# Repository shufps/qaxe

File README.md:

# NerdQ Hardware Repository

This repository contains multiple generations of small-scale Bitcoin miner hardware designs.

## NerdQAxe++

Current high-performance design based on 4× BM1370 ASICs.

- ~4.8 TH/s at ~76 W (~15.8 J/TH)
- Previous stable version (that was used for most NQ++): [rev5.1](https://github.com/shufps/qaxe/releases/tag/rev5.1)
- Latest:  [rev5.1.2](https://github.com/shufps/qaxe/releases/tag/rev5.1.2)*

*: contains some [improvements](https://github.com/shufps/qaxe/pull/31) but is untested yet.

## NerdQAxe+

Design based on 4x BM1368 ASICs.

- ~2.5TH/s at ~55 W (~22 J/TH)
- Latest revision 5.0

## Firmware for NQ+ and NQ++

The latest version can be found here:

https://github.com/shufps/ESP-Miner-NerdQAxePlus

## Legacy Designs

The following designs are **end of life** and no longer supported:

- QAxe+
- QAxe

They are provided for reference, documentation, and historical reasons only.

**No support, fixes, or updates will be provided for legacy designs.**

See `legacy/README.md` for full documentation of deprecated hardware.

---

## Compatible Replacement Parts

### For NerdQAxe++
- 25 MHz Oscillator
  Original: IQD LFSPXO076024
  Replacement: Taitien OXLTDLJANF-25.000000

### For NerdQAxe++ and NerdQAxe+
- 0.8 V LDO
  Original: Microchip MCP1824T-0802E-OT
  Replacement: TI TPS78408QDBVRQ1

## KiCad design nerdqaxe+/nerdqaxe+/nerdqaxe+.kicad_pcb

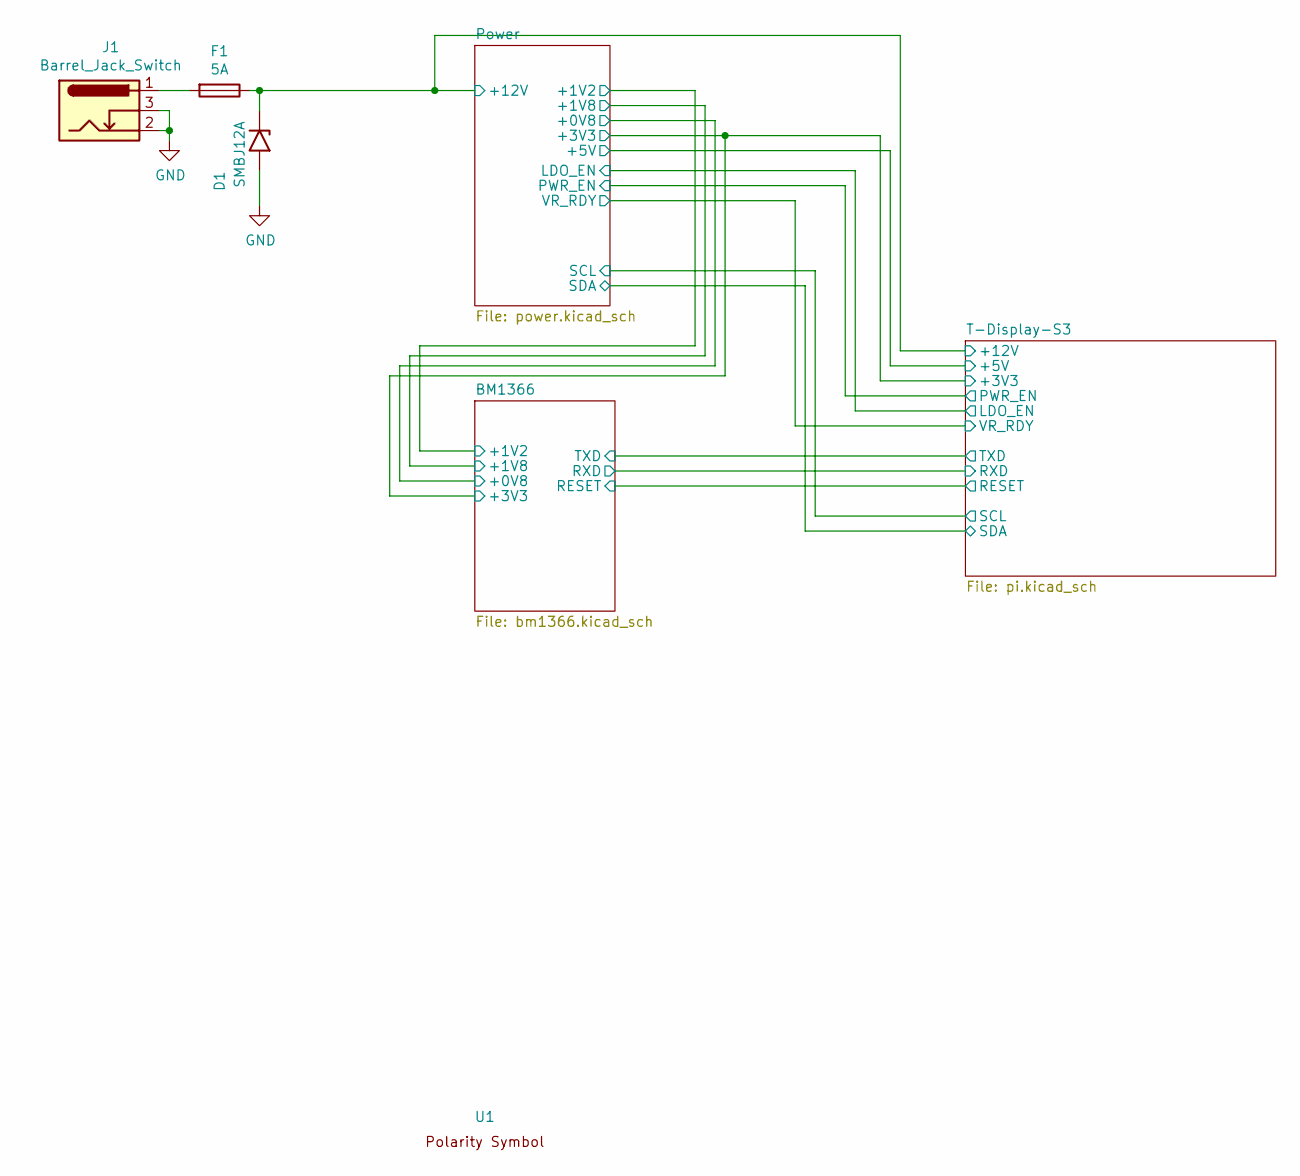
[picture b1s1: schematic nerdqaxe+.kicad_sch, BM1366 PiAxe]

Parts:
D1: SMBJ12A; D_SMB
F1: 5A; fuseholder_littlefuse_blok
J1: Barrel_Jack_Switch; BarrelJack_CUI_PJ-102AH_Horizontal
U1: polarity

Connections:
+12V: D1.1 (A1), F1.1; also elsewhere on the board
GND: D1.2 (A2), J1.2, J1.3; also elsewhere on the board
unnamed: F1.2, J1.1

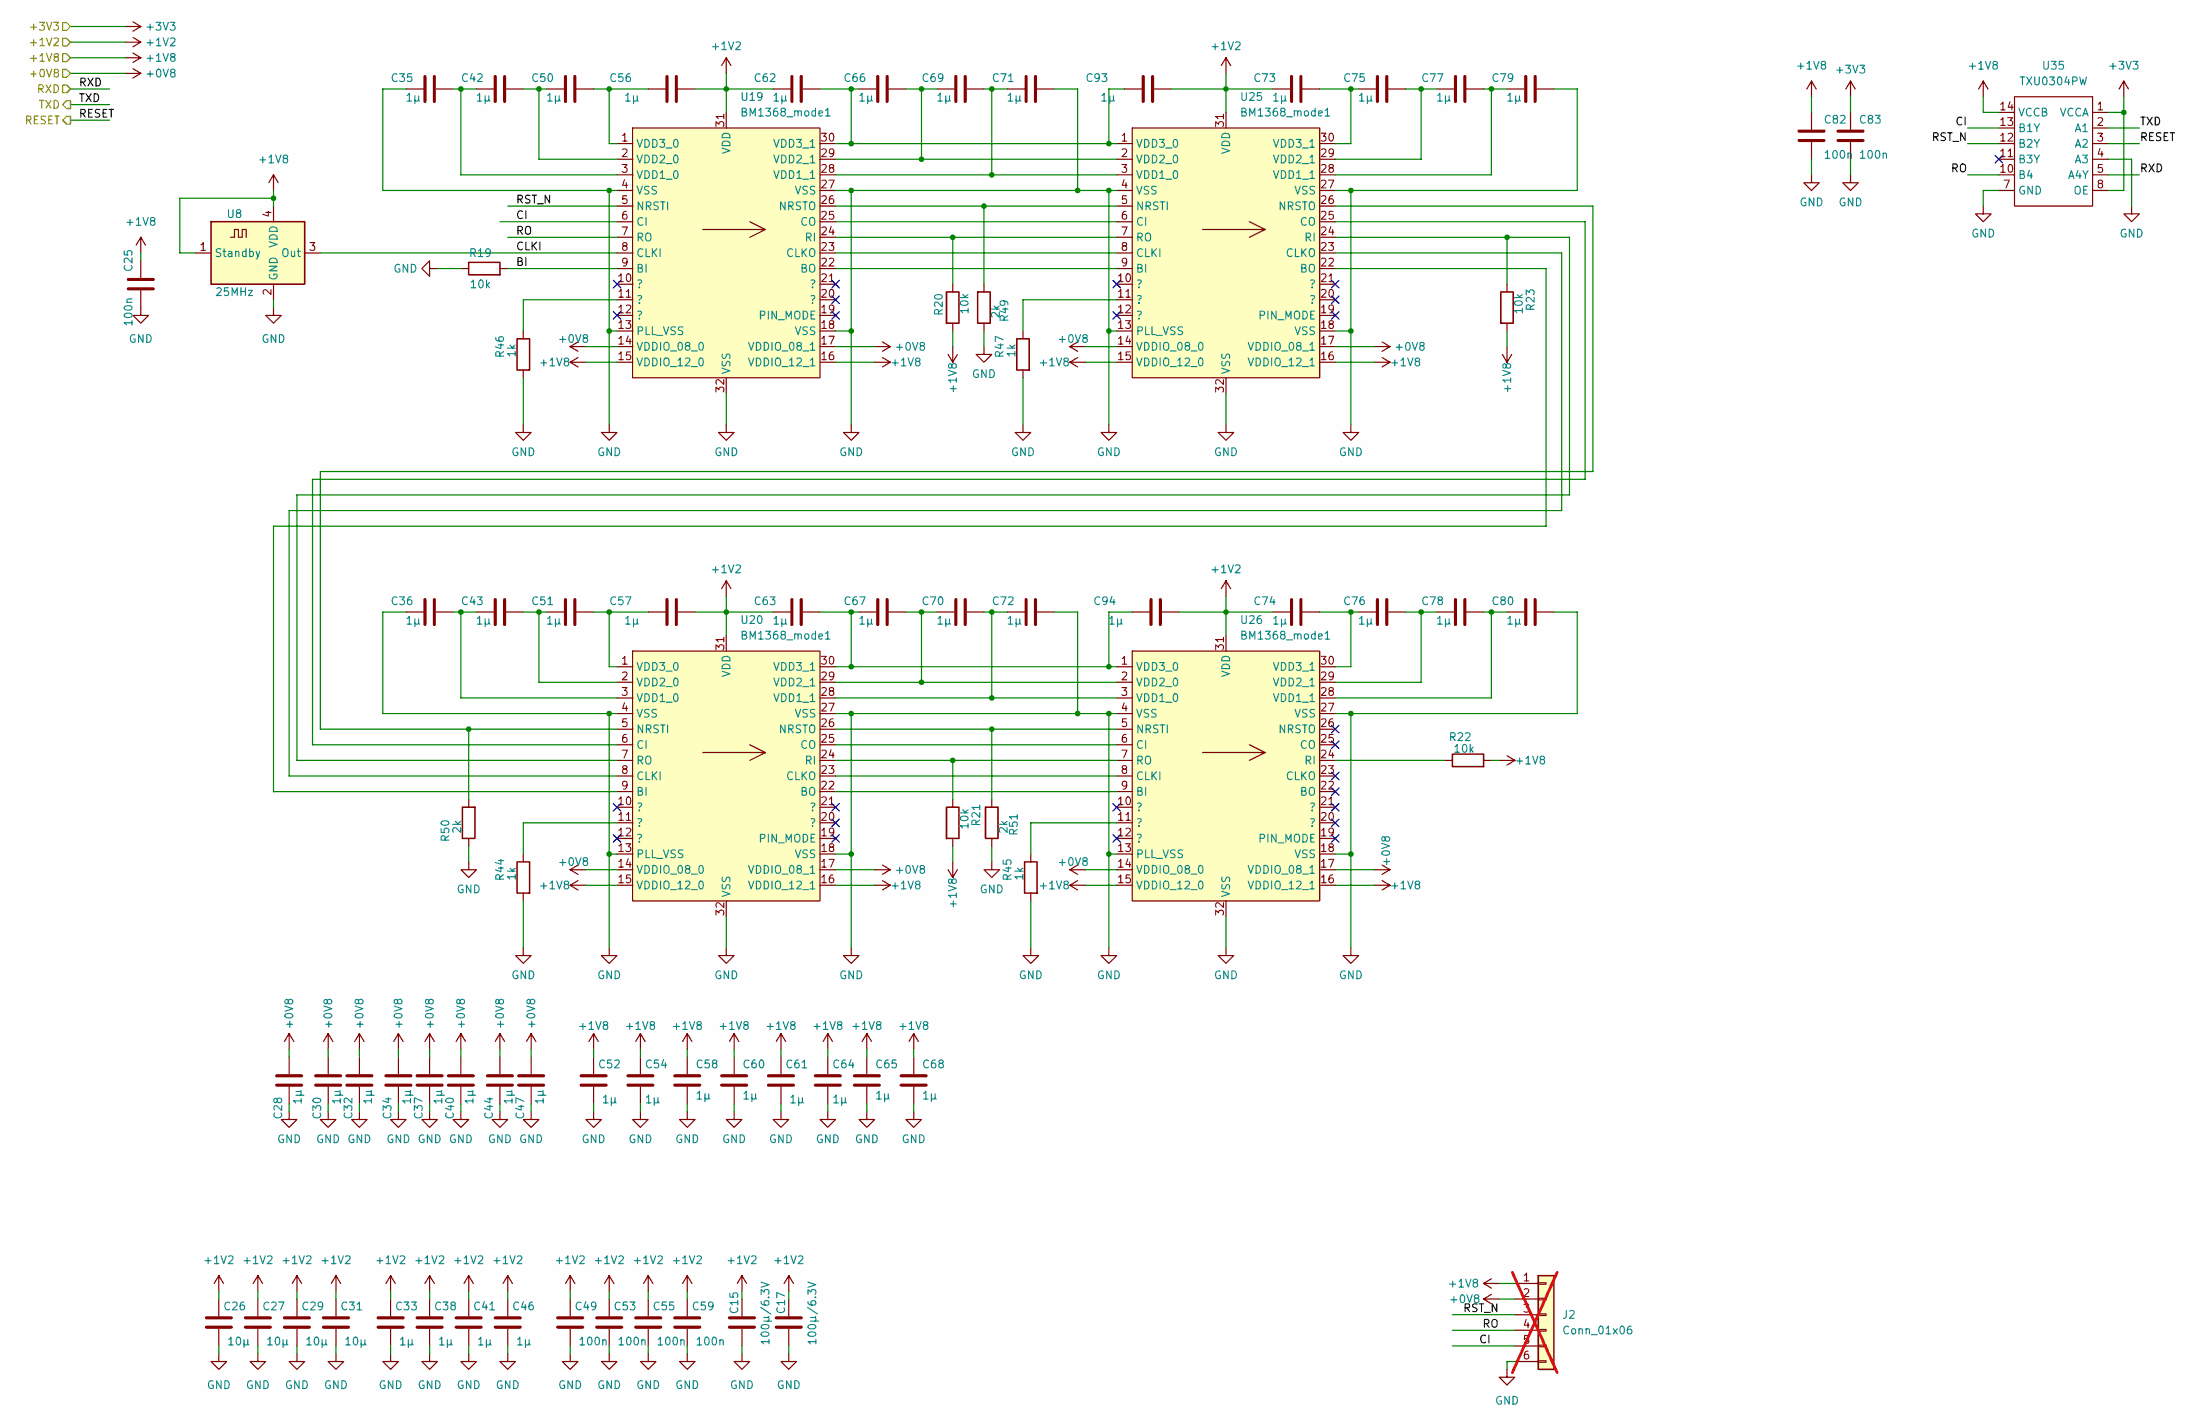
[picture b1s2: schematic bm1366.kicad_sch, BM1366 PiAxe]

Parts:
C15, C17: 100µ/6.3V; C_1210_3225Metric
C25, C49, C53, C55, C59, C82, C83: 100n; C_0805_2012Metric
C26, C27, C29, C31: 10µ; C_0805_2012Metric
C28, C30, C32, C33, C34, C35, C36, C37, C38, C40, C41, C42, C43, C44, C46, C47, C50, C51, C52, C54, C56, C57, C58, C60, C61, C62, C63, C64, C65, C66, C67, C68, C69, C70, C71, C72, C73, C74, C75, C76, C77, C78, C79, C80, C93, C94: 1µ; C_0805_2012Metric
J2: Conn_01x06; PinHeader_1x06_P1.27mm_Vertical; not fitted
R19, R20, R21, R22, R23: 10k; R_0805_2012Metric
R44, R45, R46, R47: 1k; R_0805_2012Metric
R49, R50, R51: 2k; R_0805_2012Metric
U8: 25MHz; Oscillator_SMD_EuroQuartz_XO32-4Pin_3.2x2.5mm
U19, U20, U25, U26: BM1368_mode1; bm1368-package-modified
U35: TXU0304PW; TSSOP-14_4.4x5mm_P0.65mm

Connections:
+0V8: C28.2, C30.2, C32.2, C34.2, C37.2, C40.2, C44.2, C47.2, J2.2, U19.14 (VDDIO_08_0), U19.17 (VDDIO_08_1), U20.14 (VDDIO_08_0), U20.17 (VDDIO_08_1), U25.14 (VDDIO_08_0), U25.17 (VDDIO_08_1), U26.14 (VDDIO_08_0), U26.17 (VDDIO_08_1); also elsewhere on the board
+1V2: C15.1, C17.1, C26.1, C27.1, C29.1, C31.1, C33.1, C38.1, C41.1, C46.1, C49.1, C53.1, C55.1, C56.2, C57.2, C59.1, C62.1, C63.1, C73.1, C74.1, C93.2, C94.2, U19.31 (VDD), U20.31 (VDD), U25.31 (VDD), U26.31 (VDD); also elsewhere on the board
+1V8: C25.1, C52.1, C54.1, C58.1, C60.1, C61.1, C64.1, C65.1, C68.1, C82.1, J2.1, R20.2, R21.2, R22.2, R23.2, U8.1 (Standby), U8.4 (VDD), U19.15 (VDDIO_12_0), U19.16 (VDDIO_12_1), U20.15 (VDDIO_12_0), U20.16 (VDDIO_12_1), U25.15 (VDDIO_12_0), U25.16 (VDDIO_12_1), U26.15 (VDDIO_12_0), U26.16 (VDDIO_12_1), U35.14 (VCCB); also elsewhere on the board
+3V3: C83.1, U35.1 (VCCA), U35.8 (OE); also elsewhere on the board
/BM1366/BI: R19.2, U19.9 (BI)
/BM1366/CI: J2.5, U19.6 (CI), U35.13 (B1Y)
/BM1366/CLKI: U8.3 (Out), U19.8 (CLKI)
/BM1366/RESET: U35.3 (A2); also elsewhere on the board
/BM1366/RO: J2.4, U19.7 (RO), U35.10 (B4)
/BM1366/RST_N: J2.3, U19.5 (NRSTI), U35.12 (B2Y)
/BM1366/RXD: U35.5 (A4Y); also elsewhere on the board
/BM1366/TXD: U35.2 (A1); also elsewhere on the board
GND: C15.2, C17.2, C25.2, C26.2, C27.2, C28.1, C29.2, C30.1, C31.2, C32.1, C33.2, C34.1, C35.1, C36.1, C37.1, C38.2, C40.1, C41.2, C44.1, C46.2, C47.1, C49.2, C52.2, C53.2, C54.2, C55.2, C58.2, C59.2, C60.2, C61.2, C64.2, C65.2, C68.2, C71.2, C72.2, C79.2, C80.2, C82.2, C83.2, J2.6, R19.1, R44.2, R45.2, R46.2, R47.2, R49.1, R50.1, R51.1, U8.2 (GND), U19.4 (VSS), U19.13 (PLL_VSS), U19.18 (VSS), U19.27 (VSS), U19.32 (VSS), U20.4 (VSS), U20.13 (PLL_VSS), U20.18 (VSS), U20.27 (VSS), U20.32 (VSS), U25.4 (VSS), U25.13 (PLL_VSS), U25.18 (VSS), U25.27 (VSS), U25.32 (VSS), U26.4 (VSS), U26.13 (PLL_VSS), U26.18 (VSS), U26.27 (VSS), U26.32 (VSS), U35.4 (A3), U35.7 (GND); also elsewhere on the board
unnamed: R44.1, U20.11 (?)
unnamed: R45.1, U26.11 (?)
unnamed: R46.1, U19.11 (?)
unnamed: R47.1, U25.11 (?)
unnamed: U19.22 (BO), U25.9 (BI)
unnamed: U19.23 (CLKO), U25.8 (CLKI)
unnamed: U19.25 (CO), U25.6 (CI)
unnamed: R49.2, U19.26 (NRSTO), U25.5 (NRSTI)
unnamed: R20.1, U19.24 (RI), U25.7 (RO)
unnamed: C35.2, C42.1, U19.3 (VDD1_0)
unnamed: C69.2, C71.1, U19.28 (VDD1_1), U25.3 (VDD1_0)
unnamed: C42.2, C50.1, U19.2 (VDD2_0)
unnamed: C66.2, C69.1, U19.29 (VDD2_1), U25.2 (VDD2_0)
unnamed: C50.2, C56.1, U19.1 (VDD3_0)
unnamed: C62.2, C66.1, C93.1, U19.30 (VDD3_1), U25.1 (VDD3_0)
unnamed: U20.9 (BI), U25.22 (BO)
unnamed: U20.22 (BO), U26.9 (BI)
unnamed: U20.6 (CI), U25.25 (CO)
unnamed: U20.8 (CLKI), U25.23 (CLKO)
unnamed: U20.23 (CLKO), U26.8 (CLKI)
unnamed: U20.25 (CO), U26.6 (CI)
unnamed: R50.2, U20.5 (NRSTI), U25.26 (NRSTO)
unnamed: R51.2, U20.26 (NRSTO), U26.5 (NRSTI)
unnamed: R21.1, U20.24 (RI), U26.7 (RO)
unnamed: R23.1, U20.7 (RO), U25.24 (RI)
unnamed: C36.2, C43.1, U20.3 (VDD1_0)
unnamed: C70.2, C72.1, U20.28 (VDD1_1), U26.3 (VDD1_0)
unnamed: C43.2, C51.1, U20.2 (VDD2_0)
unnamed: C67.2, C70.1, U20.29 (VDD2_1), U26.2 (VDD2_0)
unnamed: C51.2, C57.1, U20.1 (VDD3_0)
unnamed: C63.2, C67.1, C94.1, U20.30 (VDD3_1), U26.1 (VDD3_0)
unnamed: C77.2, C79.1, U25.28 (VDD1_1)
unnamed: C75.2, C77.1, U25.29 (VDD2_1)
unnamed: C73.2, C75.1, U25.30 (VDD3_1)
unnamed: R22.1, U26.24 (RI)
unnamed: C78.2, C80.1, U26.28 (VDD1_1)
unnamed: C76.2, C78.1, U26.29 (VDD2_1)
unnamed: C74.2, C76.1, U26.30 (VDD3_1)

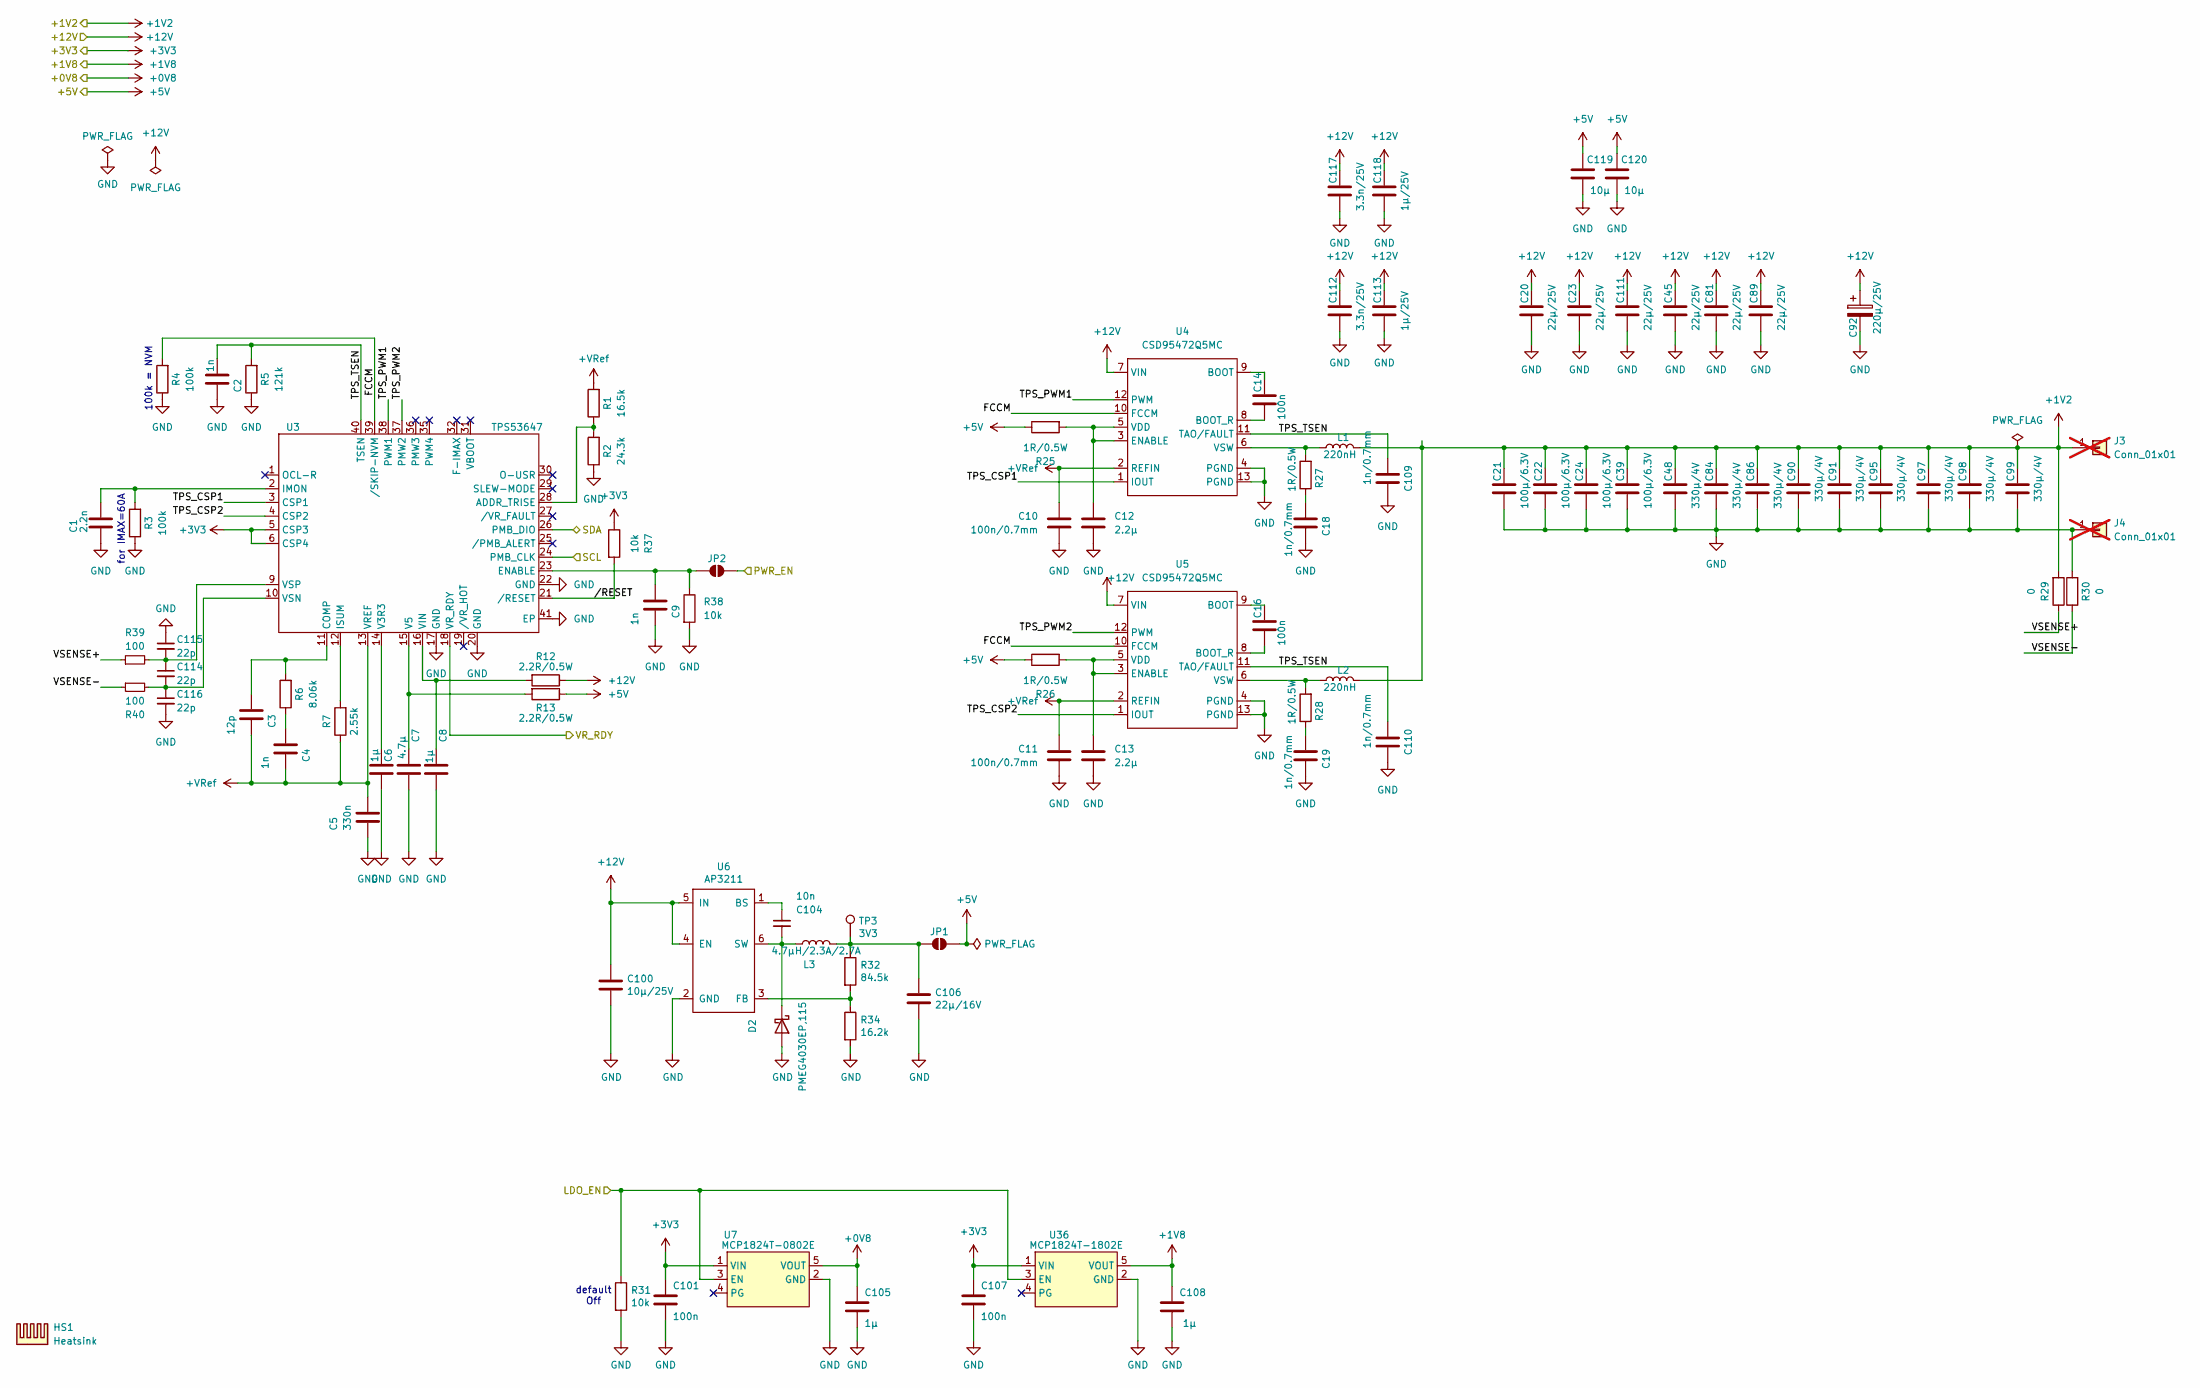
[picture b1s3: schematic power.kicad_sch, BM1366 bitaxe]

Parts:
C1: 2.2n; C_0805_2012Metric
C2, C4, C9: 1n; C_0805_2012Metric
C3: 12p; C_0603_1608Metric
C5: 330n; C_0805_2012Metric
C6, C8, C105, C108: 1µ; C_0805_2012Metric
C7: 4.7µ; C_0805_2012Metric
C10, C11: 100n/0.7mm; C_0805_2012Metric
C12, C13: 2.2µ; C_0805_2012Metric
C14, C16, C101, C107: 100n; C_0805_2012Metric
C18, C19, C109, C110: 1n/0.7mm; C_0805_2012Metric
C20, C23, C45, C81, C89, C111: 22µ/25V; C_1210_3225Metric
C21, C22, C24, C39: 100µ/6.3V; C_1210_3225Metric
C48, C84, C86, C90, C91, C95, C97, C98, C99: 330µ/4V; C_1210_3225Metric
C92: 220µ/25V; CP_Elec_8x10
C100: 10µ/25V; C_0805_2012Metric
C104: 10n; C_0805_2012Metric
C106: 22µ/16V; C_1206_3216Metric
C112, C117: 3.3n/25V; C_0805_2012Metric
C113, C118: 1µ/25V; C_0805_2012Metric
C114, C115, C116: 22p; C_0603_1608Metric
C119, C120: 10µ; C_0805_2012Metric
D2: PMEG4030EP,115; D_SOD-128
HS1: Heatsink
J3, J4: Conn_01x01; Wuerth_REDCUBE-THR_WP-THRBU_74650194_THR; not fitted
JP1, JP2: SolderJumper_2_Open; SolderJumper-2_P1.3mm_Open_RoundedPad1.0x1.5mm
L1, L2: 220nH; IFLR-4031GC-01-8x10
L3: 4.7µH/2.3A/2.7A; L_Taiyo-Yuden_NR-50xx
R1: 16.5k; R_0805_2012Metric
R2: 24.3k; R_0805_2012Metric
R3, R4: 100k; R_0805_2012Metric
R5: 121k; R_0805_2012Metric
R6: 8.06k; R_0805_2012Metric
R7: 2.55k; R_0805_2012Metric
R12, R13: 2.2R/0.5W; R_0805_2012Metric
R25, R26, R27, R28: 1R/0.5W; R_0805_2012Metric
R29, R30: 0; R_0805_2012Metric
R31, R37, R38: 10k; R_0805_2012Metric
R32: 84.5k; R_0805_2012Metric
R34: 16.2k; R_0805_2012Metric
R39, R40: 100; R_0805_2012Metric
TP3: 3V3; TestPoint_Pad_2.0x2.0mm
U3: TPS53647; Texas_RHA0040B_VQFN-40-1EP_6x6mm_P0.5mm_EP4.15x4.15mm_Therm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
U4, U5: CSD95472Q5MC; CSD95472-SON-5x6
U6: AP3211; SOT-23-6
U7: MCP1824T-0802E; SOT-23-5
U36: MCP1824T-1802E; SOT-23-5

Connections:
+0V8: C105.1, U7.5 (VOUT); also elsewhere on the board
+1V2: C21.1, C22.1, C24.1, C39.1, C48.1, C84.1, C86.1, C90.1, C91.1, C95.1, C97.1, C98.1, C99.1, J3.1, L1.2, L2.2, R29.2; also elsewhere on the board
+1V8: C108.1, U36.5 (VOUT); also elsewhere on the board
+3V3: C101.1, C107.1, R37.1, U3.5 (CSP3), U3.6 (CSP4), U7.1 (VIN), U36.1 (VIN); also elsewhere on the board
+5V: C119.1, C120.1, JP1.2 (B), R13.1, R25.1, R26.1; also elsewhere on the board
+12V: C20.1, C23.1, C45.1, C81.1, C89.1, C92.1, C100.1, C111.1, C112.1, C113.1, C117.1, C118.1, R12.1, U4.7 (VIN), U5.7 (VIN), U6.4 (EN), U6.5 (IN); also elsewhere on the board
+VRef: C3.2, C4.2, C5.1, C10.1, C11.1, R1.2, R7.1, U3.13 (VREF), U4.2 (REFIN), U5.2 (REFIN)
/Power/FCCM: R4.2, U3.39 (/SKIP-NVM), U4.10 (FCCM), U5.10 (FCCM)
/Power/LDO_EN: R31.1, U7.3 (EN), U36.3 (EN); also elsewhere on the board
/Power/PWR_EN: JP2.2 (B); also elsewhere on the board
/Power/TPS_CSP1: U3.3 (CSP1), U4.1 (IOUT)
/Power/TPS_CSP2: U3.4 (CSP2), U5.1 (IOUT)
/Power/TPS_PWM1: U3.38 (PWM1), U4.12 (PWM)
/Power/TPS_PWM2: U3.37 (PMW2), U5.12 (PWM)
/Power/TPS_TSEN: C2.1, C109.1, C110.1, R5.2, U3.40 (TSEN), U4.11 (TAO/FAULT), U5.11 (TAO/FAULT)
/Power/VR_RDY: U3.18 (VR_RDY); also elsewhere on the board
/Power/VSENSE+: R29.1, R39.1
/Power/VSENSE-: R30.1, R40.1
/Power//RESET: R37.2, U3.21 (/RESET)
/T-Display-S3/SCL: U3.24 (PMB_CLK); also elsewhere on the board
/T-Display-S3/SDA: U3.26 (PMB_DIO); also elsewhere on the board
GND: C1.2, C2.2, C5.2, C6.2, C7.1, C8.1, C9.2, C10.2, C11.2, C12.2, C13.2, C18.2, C19.2, C20.2, C21.2, C22.2, C23.2, C24.2, C39.2, C45.2, C48.2, C81.2, C84.2, C86.2, C89.2, C90.2, C91.2, C92.2, C95.2, C97.2, C98.2, C99.2, C100.2, C101.2, C105.2, C106.2, C107.2, C108.2, C109.2, C110.2, C111.2, C112.2, C113.2, C115.1, C116.2, C117.2, C118.2, C119.2, C120.2, D2.2 (A), J4.1, R2.1, R3.1, R4.1, R5.1, R30.2, R31.2, R34.2, R38.2, U3.17 (GND), U3.20 (GND), U3.22 (GND), U3.41 (EP), U4.4 (PGND), U4.13 (PGND), U5.4 (PGND), U5.13 (PGND), U6.2 (GND), U7.2 (GND), U36.2 (GND); also elsewhere on the board
unnamed: C4.1, R6.1
unnamed: C18.1, R27.1
unnamed: C19.1, R28.1
unnamed: C104.2, D2.1 (K), L3.1, U6.6 (SW)
unnamed: C106.1, JP1.1 (A), L3.2, R32.1, TP3.1
unnamed: C9.1, JP2.1 (A), R38.1, U3.23 (ENABLE)
unnamed: R1.1, R2.2, U3.28 (ADDR_TRISE)
unnamed: C3.1, R6.2, U3.11 (COMP)
unnamed: C1.1, R3.2, U3.2 (IMON)
unnamed: R7.2, U3.12 (ISUM)
unnamed: C6.1, U3.14 (V3R3)
unnamed: C7.2, R13.2, U3.15 (V5)
unnamed: C8.2, R12.2, U3.16 (VIN)
unnamed: C114.2, C116.1, R40.2, U3.10 (VSN)
unnamed: C114.1, C115.2, R39.2, U3.9 (VSP)
unnamed: C14.1, U4.9 (BOOT)
unnamed: C14.2, U4.8 (BOOT_R)
unnamed: C12.1, R25.2, U4.3 (ENABLE), U4.5 (VDD)
unnamed: L1.1, R27.2, U4.6 (VSW)
unnamed: C16.1, U5.9 (BOOT)
unnamed: C16.2, U5.8 (BOOT_R)
unnamed: C13.1, R26.2, U5.3 (ENABLE), U5.5 (VDD)
unnamed: L2.1, R28.2, U5.6 (VSW)
unnamed: C104.1, U6.1 (BS)
unnamed: R32.2, R34.1, U6.3 (FB)

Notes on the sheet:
default Off
for IMAX=60A
100k = NVM

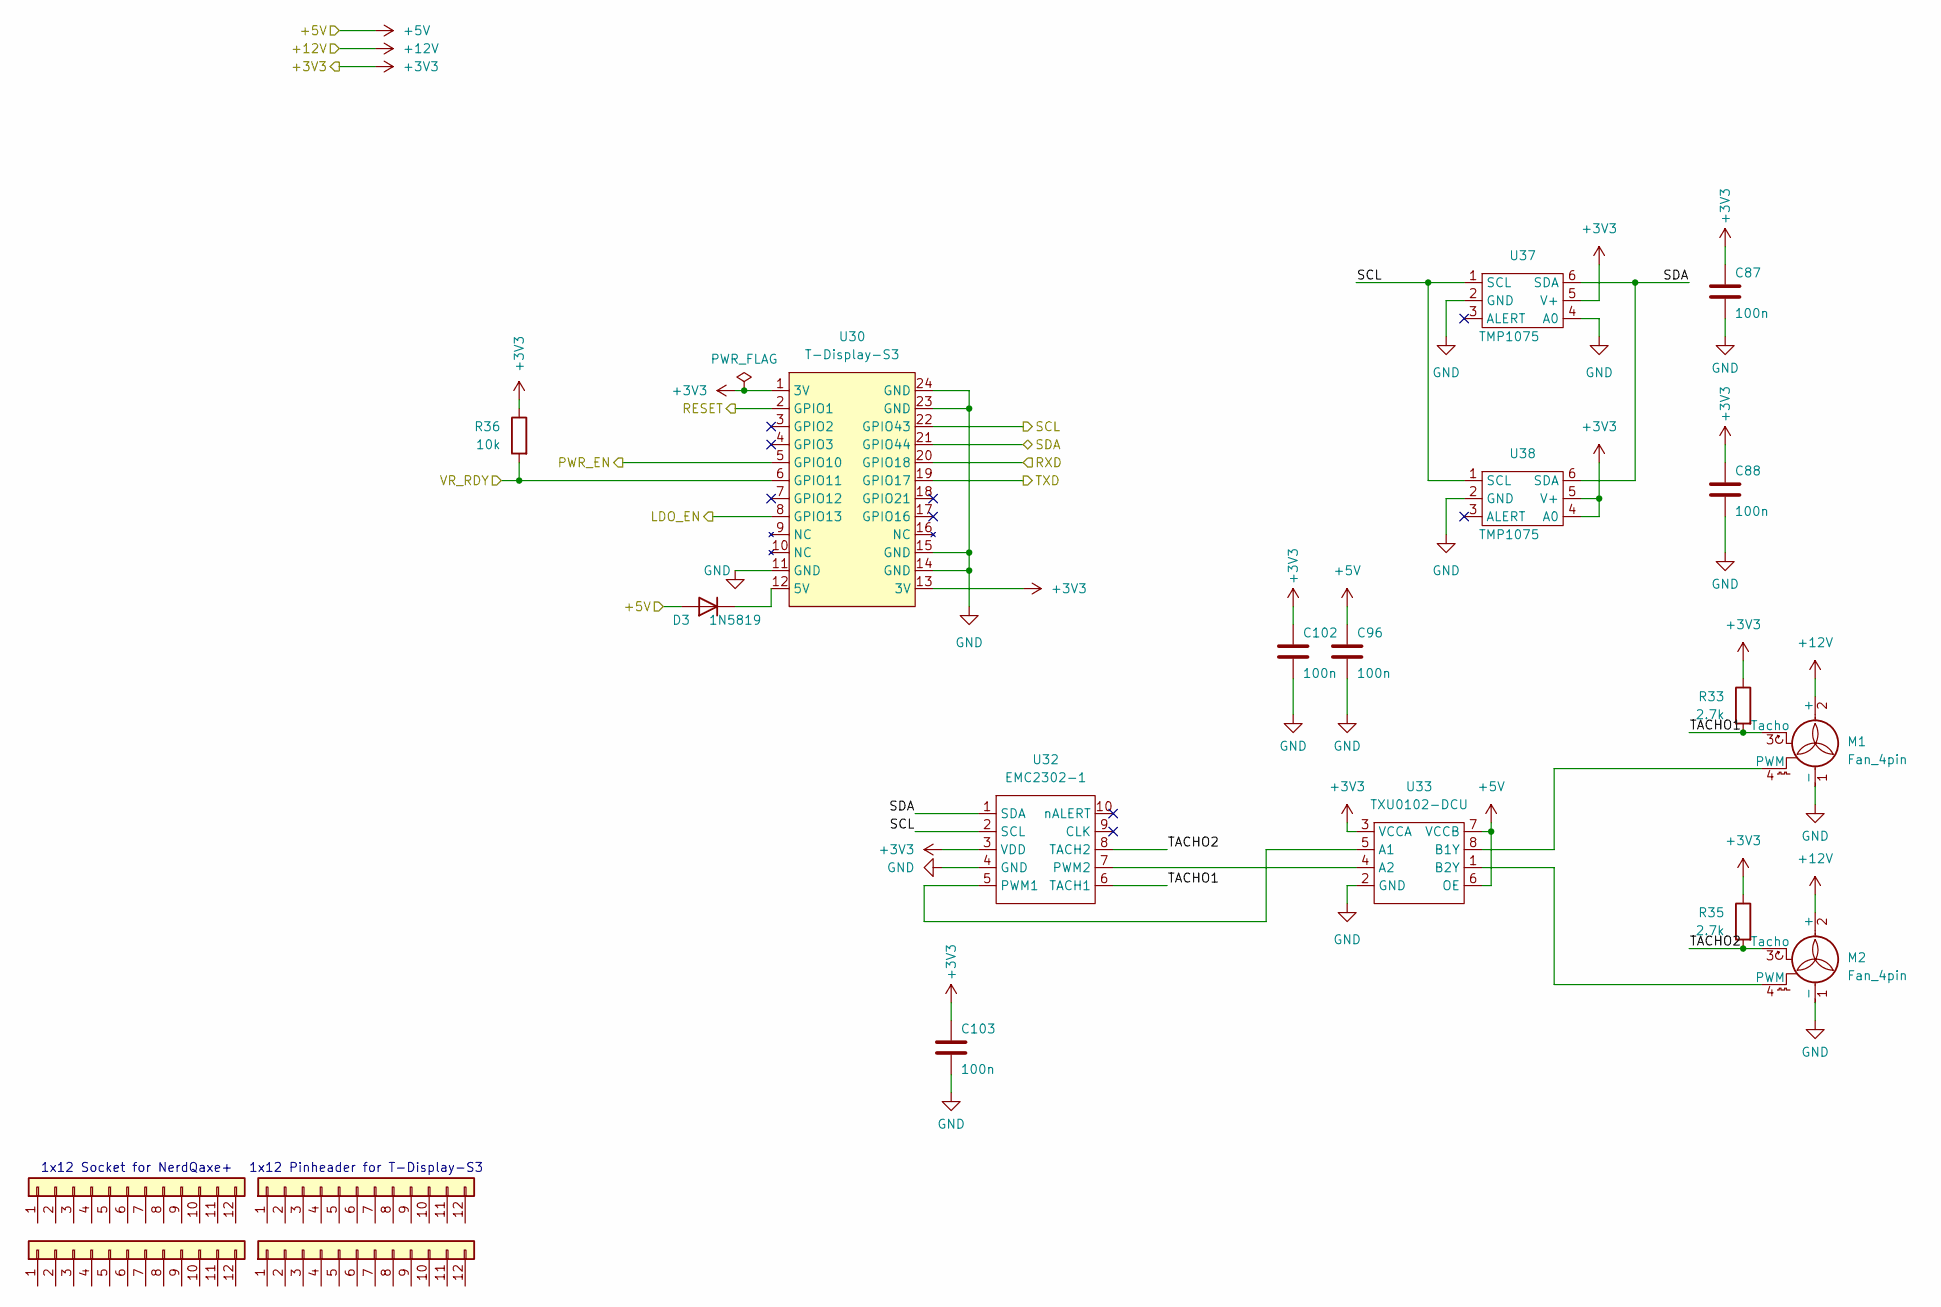
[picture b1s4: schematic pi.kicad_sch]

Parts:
C87, C88, C96, C102, C103: 100n; C_0805_2012Metric
D3: 1N5819; D_SOD-123
J5, J6: Conn_01x12-Socket
J7, J8: Conn_01x12-Header
M1, M2: Fan_4pin; FanPinHeader_1x04_P2.54mm_Vertical
R33, R35: 2.7k; R_0805_2012Metric
R36: 10k; R_0805_2012Metric
U30: T-Display-S3
U32: EMC2302-1; MSOP-10_3x3mm_P0.5mm
U33: TXU0102-DCU; VSSOP-8_2.3x2mm_P0.5mm
U37, U38: TMP1075; TMP1075-DRL

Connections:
+3V3: C87.1, C88.1, C102.1, C103.1, R33.1, R35.1, R36.1, U30.1 (3V), U30.13 (3V), U32.3 (VDD), U33.3 (VCCA), U37.5 (V+), U38.4 (A0), U38.5 (V+); also elsewhere on the board
+5V: C96.1, D3.2 (A), U33.6 (OE), U33.7 (VCCB); also elsewhere on the board
+12V: M1.2 (+), M2.2 (+); also elsewhere on the board
/BM1366/RESET: U30.2 (GPIO1); also elsewhere on the board
/BM1366/RXD: U30.20 (GPIO18); also elsewhere on the board
/BM1366/TXD: U30.19 (GPIO17); also elsewhere on the board
/Power/LDO_EN: U30.8 (GPIO13); also elsewhere on the board
/Power/PWR_EN: U30.5 (GPIO10); also elsewhere on the board
/Power/VR_RDY: R36.2, U30.6 (GPIO11); also elsewhere on the board
/T-Display-S3/SCL: U30.22 (GPIO43), U32.2 (SCL), U37.1 (SCL), U38.1 (SCL); also elsewhere on the board
/T-Display-S3/SDA: U30.21 (GPIO44), U32.1 (SDA), U37.6 (SDA), U38.6 (SDA); also elsewhere on the board
/T-Display-S3/TACHO1: M1.3 (Tacho), R33.2, U32.6 (TACH1)
/T-Display-S3/TACHO2: M2.3 (Tacho), R35.2, U32.8 (TACH2)
GND: C87.2, C88.2, C96.2, C102.2, C103.2, M1.1 (-), M2.1 (-), U30.11 (GND), U30.14 (GND), U30.15 (GND), U30.23 (GND), U30.24 (GND), U32.4 (GND), U33.2 (GND), U37.2 (GND), U37.4 (A0), U38.2 (GND); also elsewhere on the board
unnamed: D3.1 (K), U30.12 (5V)
unnamed: M1.4 (PWM), U33.8 (B1Y)
unnamed: M2.4 (PWM), U33.1 (B2Y)
unnamed: U32.5 (PWM1), U33.5 (A1)
unnamed: U32.7 (PWM2), U33.4 (A2)

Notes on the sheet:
1x12 Socket for NerdQaxe+
1x12 Pinheader for T-Display-S3

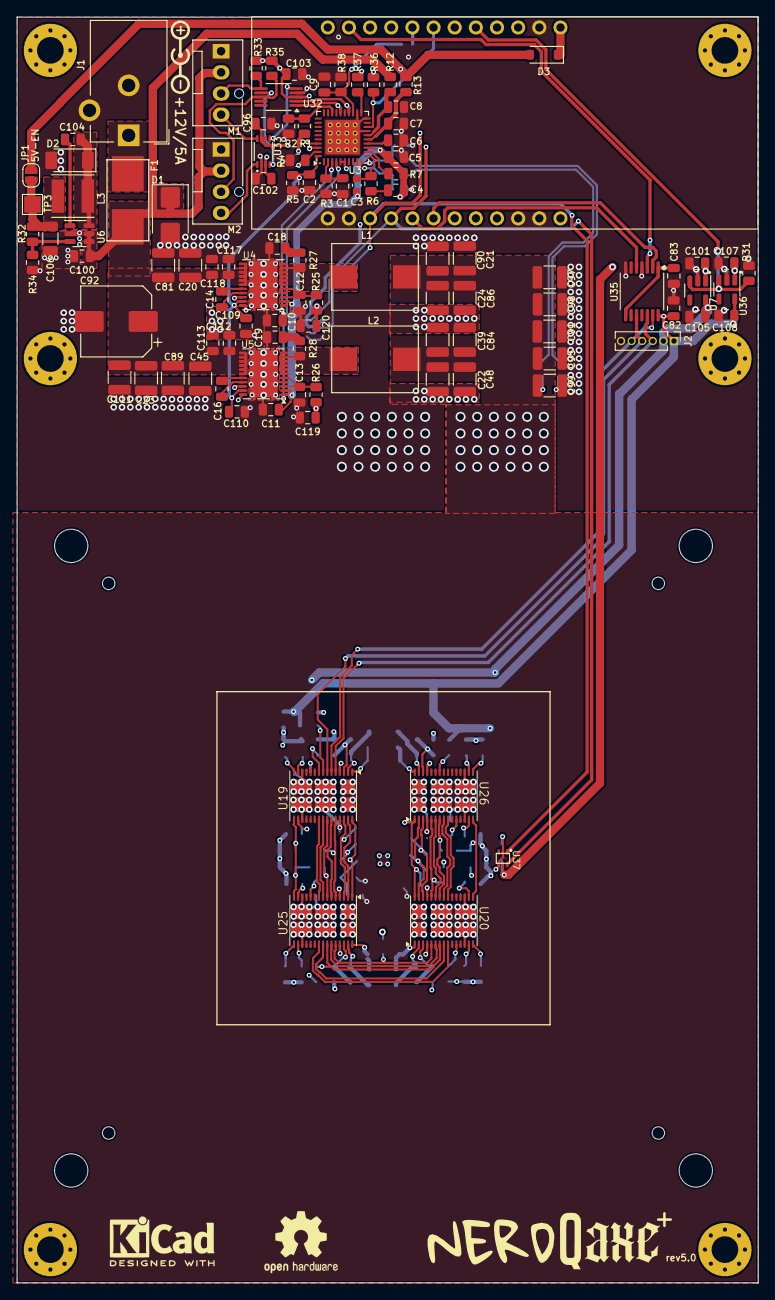
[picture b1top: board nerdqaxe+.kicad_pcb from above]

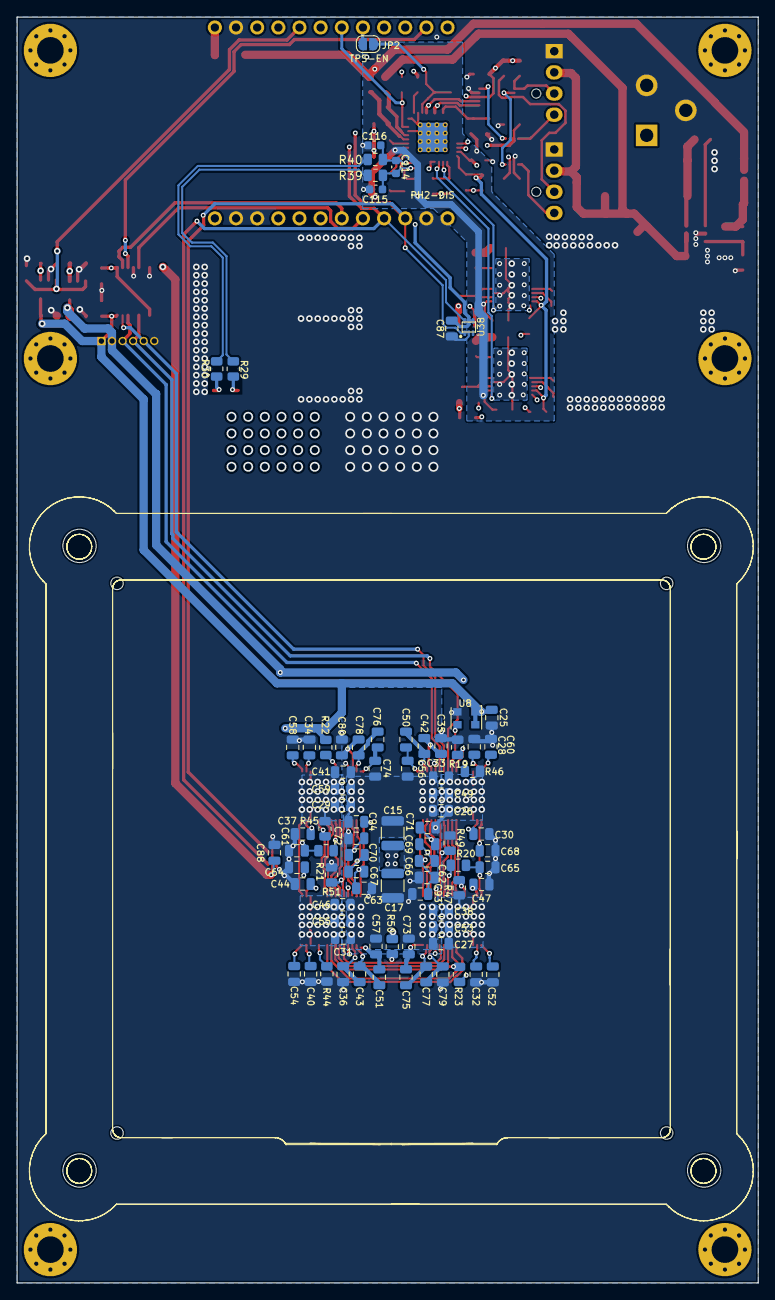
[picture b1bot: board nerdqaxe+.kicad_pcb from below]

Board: 4 copper layers, 89.0 x 152.0 mm, 188 parts (81 on the bottom side), 101 nets.
